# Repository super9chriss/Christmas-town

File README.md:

# "Smart"christmas town
A ESP32 C6 based Christmas town which connects to homeautomation to be able to remotly turn on and off the christmas lights
<div align="center">

</div>

## Features

* **Microcontroller:** ESP32-C6-Zero
* **Power Input:** 12V DC
* **supported** it works with 3 3V, 2 4.5V and one 12V houses/street lights but you can add more or use less based on youre christmas town
* **Connectivity:** USB-C receptacle for easy firmware flashing.

## PCB and schematic
| **PCB Layout** | **Schematic** |
| :---: | :---: |
||

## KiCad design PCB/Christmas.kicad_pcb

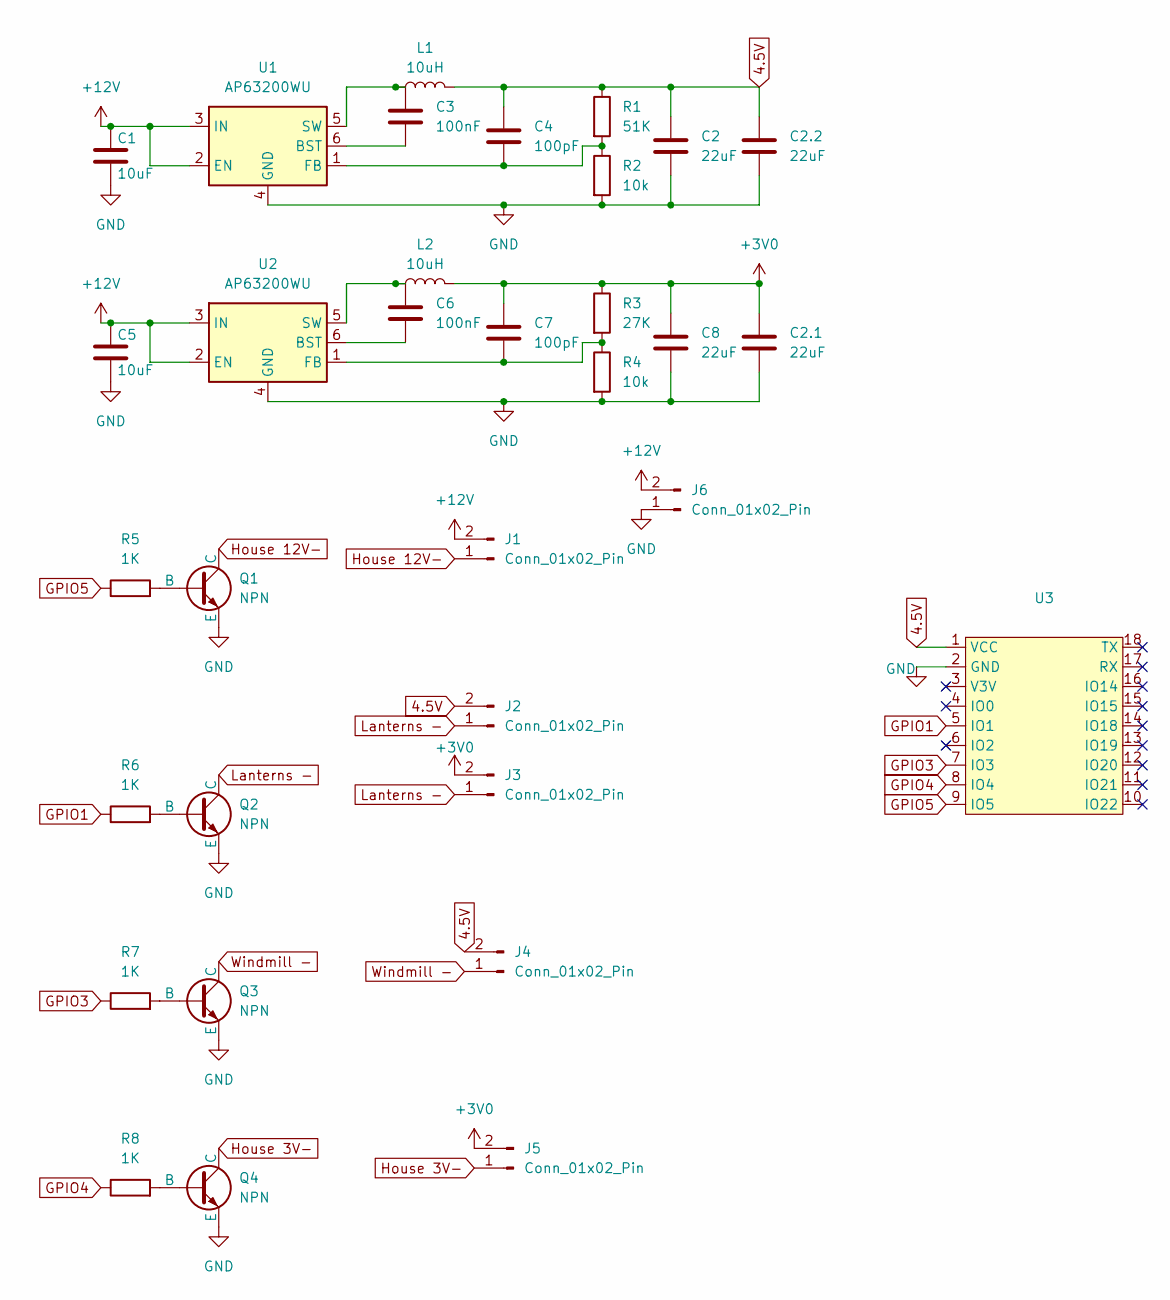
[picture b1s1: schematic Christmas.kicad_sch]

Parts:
C1, C5: 10uF; C_0603_1608Metric
C2, C2.1, C2.2, C8: 22uF; C_0603_1608Metric
C3, C6: 100nF; C_0603_1608Metric
C4, C7: 100pF; C_0603_1608Metric
J1, J2, J3, J4, J5, J6: Conn_01x02_Pin; SolderWire-0.1sqmm_1x02_P3.6mm_D0.4mm_OD1mm
L1, L2: 10uH; L_Bourns-SRN8040_8x8.15mm
Q1, Q2, Q3, Q4: NPN; TO92254P470H750-3
R1: 51K; R_0603_1608Metric
R2, R4: 10k; R_0603_1608Metric
R3: 27K; R_0603_1608Metric
R5, R6, R7, R8: 1K; R_0603_1608Metric
U1, U2: AP63200WU; TSOT-23-6_HandSoldering
U3: Waveshare-ESP32-C6-Zero

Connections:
4.5V: C2.1, C2.2.1, C4.1, J2.2, J4.2, L1.2, R1.1, U3.1 (VCC)
+3V0: C2.1.1, C7.1, C8.1, J3.2, J5.2, L2.2, R3.1
+12V: C1.1, C5.1, J1.2, J6.2, U1.2 (EN), U1.3 (IN), U2.2 (EN), U2.3 (IN)
GND: C1.2, C2.2, C2.1.2, C2.2.2, C5.2, C8.2, J6.1, Q1.3 (E), Q2.3 (E), Q3.3 (E), Q4.3 (E), R2.2, R4.2, U1.4 (GND), U2.4 (GND), U3.2 (GND)
GPIO1: R6.1, U3.5 (IO1)
GPIO3: R7.1, U3.7 (IO3)
GPIO4: R8.1, U3.8 (IO4)
GPIO5: R5.1, U3.9 (IO5)
House 3V-: J5.1, Q4.1 (C)
House 12V-: J1.1, Q1.1 (C)
Lanterns -: J2.1, J3.1, Q2.1 (C)
unnamed: Q1.2 (B), R5.2
unnamed: Q2.2 (B), R6.2
unnamed: Q3.2 (B), R7.2
unnamed: Q4.2 (B), R8.2
unnamed: C3.2, U1.6 (BST)
unnamed: C4.2, R1.2, R2.1, U1.1 (FB)
unnamed: C3.1, L1.1, U1.5 (SW)
unnamed: C6.2, U2.6 (BST)
unnamed: C7.2, R3.2, R4.1, U2.1 (FB)
unnamed: C6.1, L2.1, U2.5 (SW)
Windmill -: J4.1, Q3.1 (C)

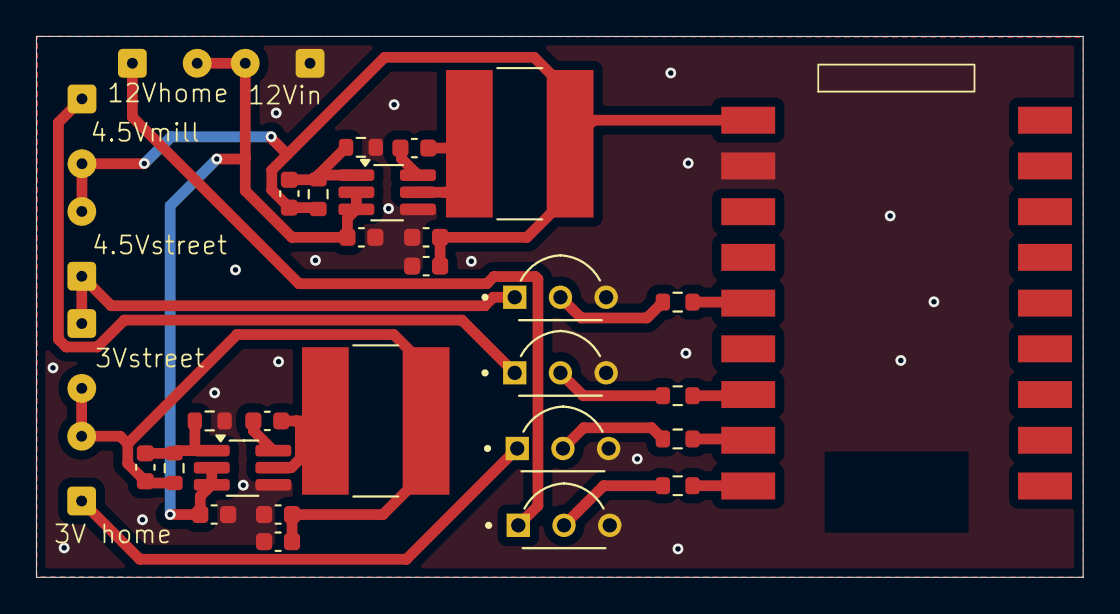
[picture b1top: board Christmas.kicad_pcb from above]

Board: 2 copper layers, 58.2 x 30.1 mm, 33 parts (0 on the bottom side), 22 nets.

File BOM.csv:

Description,quantity,price,link,,,,,,,,,,
LCSC parts,1,3.71 + 3 (handeling),see  under here,,,,,,,,,,
esp32-c6,1,5.99,https://nl.aliexpress.com/item/1005007349377720.html?spm=a2g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,,,,,,,,,,
12V adapter,1,2.62,http://nl.aliexpress.com/item/1005007264933490.html?spm=a2g0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,,,,,,,,,,
PCB,1,3.01,https://cart.jlcpcb.com/quote?stencilLayer=2&stencilWidth=10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,,,,,,,,,,
,total:,? 18.33 ÷ $22,,,,,,,,,,,
,,,,,,,,,,,,,
LCSC parts:,,,,,,,,,,,,,
Index,LCSC#,MPN,Manufacturer,Package,Customer #,Description,RoHS,Quantity,MOQ,Multiple,Unit Price(?),Extended Price(?),Product Link
1,C85864,GCM188R71H104KA57D,muRata,603,"C3,C6",100nF ñ10% 50V Ceramic Capacitor X7R 0603,yes,50,50,50,0.0096,0.48,https://www.lcsc.com/product-detail/C85864.html
2,C55722,0603CG101F500NT,FH,603,"C4,C7",100pF ñ1% 50V Ceramic Capacitor C0G 0603,yes,50,50,50,0.0089,0.45,https://www.lcsc.com/product-detail/C55722.html
3,C95204,RT0603BRD0710KL,YAGEO,603,"R2,R4",100mW 10kê 75V Thin Film Resistor ñ25ppm/? ñ0.1% 0603 Chip Resistor - Surface Mount RoHS,yes,20,20,20,0.0188,0.38,https://www.lcsc.com/product-detail/C95204.html
4,C70225,0603X106K160NT,FH,603,"C1,C5",10uF ñ10% 16V Ceramic Capacitor X5R 0603,yes,10,10,10,0.0196,0.2,https://www.lcsc.com/product-detail/C70225.html
5,C142104,LVS808040-100M-N,Chilisin,"SMD,8x8mm","L1,L2","3.42A 10uH ñ20% 49.4mê Magnetic Shielded Inductor SMD,8x8mm Fixed Inductors RoHS",yes,5,5,5,0.0997,0.5,https://www.lcsc.com/product-detail/C142104.html
6,C21190,0603WAF1001T5E,UNI-ROYAL,603,"R5,R6,R7,R8",1kê ñ1% 100mW 0603 Thick Film Resistor,yes,100,100,100,0.0011,0.11,https://www.lcsc.com/product-detail/C21190.html
7,C60077,0603X226M100NT,FH,603,"C2,C2.1,C2.2,C8",22uF ñ20% 10V Ceramic Capacitor X5R 0603,yes,10,10,10,0.0143,0.14,https://www.lcsc.com/product-detail/C60077.html
8,C22967,0603WAF2702T5E,UNI-ROYAL,603,R3,27kê ñ1% 100mW 0603 Thick Film Resistor,yes,100,100,100,0.0012,0.12,https://www.lcsc.com/product-detail/C22967.html
9,C23196,0603WAF5102T5E,UNI-ROYAL,603,R1,51kê ñ1% 100mW 0603 Thick Film Resistor,yes,100,100,100,0.0011,0.11,https://www.lcsc.com/product-detail/C23196.html
10,C2071868,AP63200WU-7,DIODES,TSOT-23-6,"U1,U2",500kHz Buck Adjustable 2A TSOT-23-6 Voltage Regulators - DC DC Switching Regulators RoHS,yes,2,1,1,0.3471,0.69,https://www.lcsc.com/product-detail/C2071868.html
11,C118536,2N2222A,ST(Semtech),TO-92,"Q1,Q2,Q3,Q4",Bipolar (BJT) Transistor NPN 40V 600mA 250MHz 625mW Through Hole TO-92,yes,20,20,20,0.0264,0.53,https://www.lcsc.com/product-detail/C118536.html

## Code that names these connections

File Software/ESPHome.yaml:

esphome:
  name: christmas-village-controller
  friendly_name: Christmas Village Controller

esp32:
  board: esp32-c6-devkitm-1 
  variant: esp32c6
  framework:
    type: esp-idf
    version: 5.3.1 


wifi:
  ssid: "name"
  password: "ww"

api:
ota:
  - platform: esphome

switch:
  - platform: gpio
    pin: GPIO5
    name: "12V house"
    id: house_12v
    restore_mode: RESTORE_DEFAULT_OFF

  - platform: gpio
    pin: GPIO1
    name: "street light (3V & 4.5V)"
    id: lanterns_mix
    restore_mode: RESTORE_DEFAULT_OFF

  - platform: gpio
    pin: GPIO3
    name: "windmill (4.5V)"
    id: windmill
    restore_mode: RESTORE_DEFAULT_OFF

  - platform: gpio
    pin: GPIO4
    name: "3V house"
    id: house_3v
    restore_mode: RESTORE_DEFAULT_OFF

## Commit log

2026-01-11 version 1
